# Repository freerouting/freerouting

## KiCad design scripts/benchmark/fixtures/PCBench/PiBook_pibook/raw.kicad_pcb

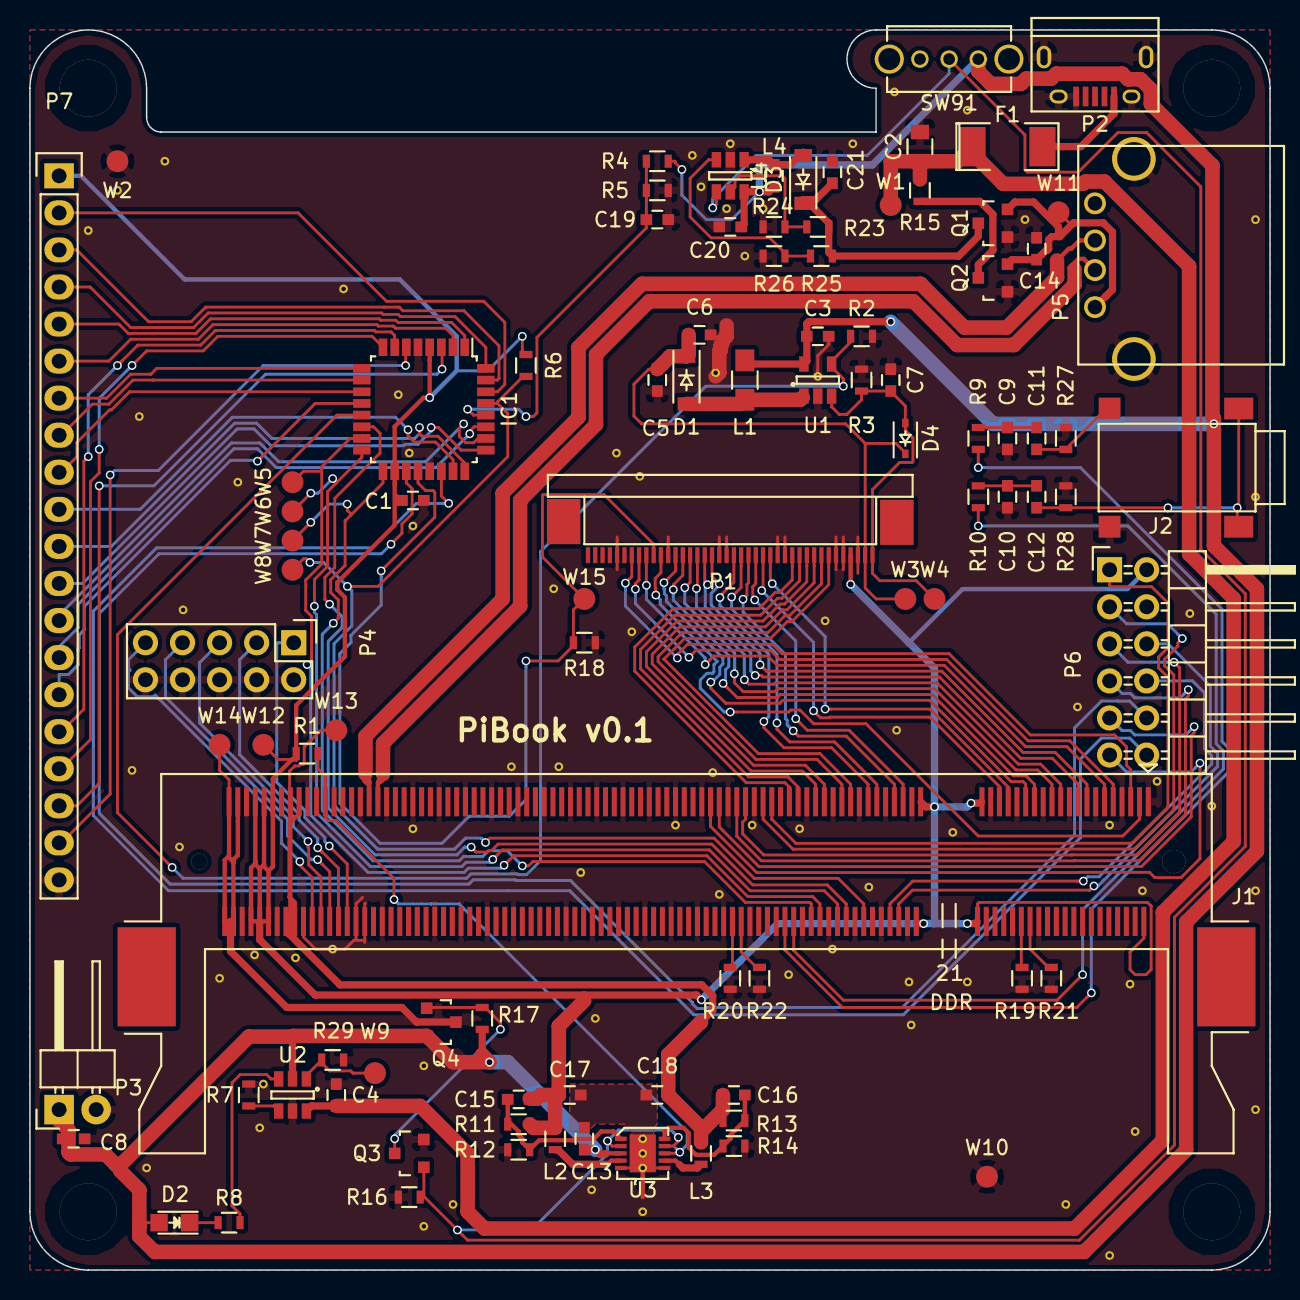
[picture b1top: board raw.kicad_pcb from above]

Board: 2 copper layers, 85.0 x 85.0 mm, 98 parts (0 on the bottom side), 103 nets.

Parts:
C1, C4, C5, C6, C7, C8, C11, C12, C20, C21: 1u; C_0603
C2: 22u; C_0805
C3: 4.7u; C_0603
C9, C10: 82n; C_0603
C13, C14, C17, C18: 10u; C_0603
C15, C16: 18p; C_0603
C19: 100n; C_0603
D1, D3: MBR0540T3G; SOD-123
D2: LED; LED_0805
D4: MM32Z24VT1G; SOD-323
F1: 2A; SMD-2010_Pol
IC1: ATTINY48-A; LQFP-32_7x7mm_Pitch0.8mm
J1: ComputeModule; Socket_SODIMM_DDR1-2_TE_1612618
J2: TRS_JACK_3PIN; TRS_3_SMD
L1: 6.8u; R_0805_HandSoldering
L2, L3: 2.2u; R_0603
L4: 10u; C_0603
MH1, MH2, MH3, MH4: Mounting_Hole; Mounting_hole_M3.5
P1: CONN_01X40; FPC40_BOTTOM
P2: USB_OTG; USB_Micro-B
P3: CONN_01X02; Pin_Header_Angled_1x02
P4: CONN_02X05; Pin_Header_Straight_2x05
P5: USB_A
P6: CONN_02X06; Pin_Header_Angled_2x06
P7: CONN_01X20; Pin_Header_Straight_1x20
Q1, Q2, Q4: Si2323DS; SOT-23
Q3: BSS138P; SOT-23
R1, R2, R4, R5, R6, R12, R14, R16, R17, R18, R19, R20, R21, R22, R27, R28: 100k; R_0603
R3: 12; R_0603
R7: 680; R_0603
R8: R; R_0603
R9, R10: 100; R_0603
R11: 450k; R_0603
R13: 200k; R_0603
R15: 0; R_0603
R23: 47k; R_0603
R24, R26, R29: 10k; R_0603
R25: 40k; R_0603
SW91: SPST; SPDT_SLIDE_SWITCH
TP1: Tie_point; tiepoint-0.3
U1: FAN5333; SOT-23-5
U2: BQ21040; SOT-23-6
U3: NCP1532; UDFN-10
U4: MIC2619YD6; SOT-23-6
W1: USB_VIN+; Measurement_Point_Round-SMD-Pad_Small
W2: USB_VIN-; Measurement_Point_Round-SMD-Pad_Small
W3: BACKL_A; Measurement_Point_Round-SMD-Pad_Small
W4: BACKL_K; Measurement_Point_Round-SMD-Pad_Small
W5, W6, W7, W8, W15: TEST_1P; Measurement_Point_Round-SMD-Pad_Small
W9: TS; Measurement_Point_Round-SMD-Pad_Small
W10: GND; Measurement_Point_Round-SMD-Pad_Small
W11: VUSB_OUT; Measurement_Point_Round-SMD-Pad_Small
W12: +3V3; Measurement_Point_Round-SMD-Pad_Small
W13: +1V8; Measurement_Point_Round-SMD-Pad_Small
W14: CM_VBAT; Measurement_Point_Round-SMD-Pad_Small

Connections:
+1V8: C16.1, C18.1, J1.183, J1.184, J1.185, J1.186, L3.2, R13.1, W13.1
+3V3: C1.1, C15.1, C17.1, IC1.4, IC1.18, J1.2, J1.39, J1.40, J1.41, J1.42, J1.189, J1.190, J1.191, J1.192, J1.193, J1.194, L2.2, P1.4, P6.2, P7.1, R1.1, R6.1, R11.1, W12.1
+5V: C21.1, D3.1, Q1.3, R23.1, R25.1
+BATT: C3.1, C8.1, C13.1, C20.1, D2.2, L1.1, L4.1, P3.1, Q4.2, R4.1, R17.1, SW91.1, U1.5, U2.2, U3.3, U4.6
+VUSB_IN: C2.1, C4.1, F1.1, R15.2, U2.6, W1.1
+VUSB_OUT: C14.1, P5.1, Q1.2, Q2.2, W11.1
/ANALOG0: IC1.19, P6.10
/ANALOG1: IC1.22, P6.12
/AUDIO_L_PWM: J1.70, R10.2
/AUDIO_R_PWM: J1.72, R9.2
/AVR_MISO: IC1.16, J1.60, W6.1
/AVR_MOSI: IC1.15, J1.64, W5.1
/AVR_SCK: IC1.17, J1.66, W7.1
/AVR_~CS: IC1.14, J1.58
/AVR_~RST: IC1.29, J1.54, R6.2, W8.1
/BACKL_A: C5.1, C6.1, D1.1, D4.1, P1.2, W3.1
/BACKL_K: C7.1, D4.2, P1.1, R3.1, U1.3, W4.1
/BACKL_PWM: IC1.13, R2.1, U1.4
/CM_RUN: J1.177, R1.2, U3.8
/CM_VBAT: J1.197, J1.198, J1.199, J1.200, Q4.3, W14.1
/KEY_C0: IC1.30, P7.2
/KEY_C1: IC1.31, P7.3
/KEY_C2: IC1.32, P7.4
/KEY_C3: IC1.1, P7.5
/KEY_C4: IC1.2, P7.6
/KEY_C5: IC1.9, P7.7
/KEY_C6: IC1.10, P7.8
/KEY_C7: IC1.11, P7.9
/KEY_C8: IC1.23, P7.10
/KEY_C9: IC1.24, P7.11
/KEY_C10: IC1.25, P7.12
/KEY_C11: IC1.26, P7.13
/KEY_R0: IC1.27, P7.14
/KEY_R1: IC1.12, P7.15
/KEY_R2: IC1.7, P7.16
/KEY_R3: IC1.8, P7.17
/KEY_R4: IC1.3, P7.18
/KEY_R5: IC1.6, P7.19
/LCD_B_2: J1.15, P1.23
/LCD_B_3: J1.17, P1.24
/LCD_B_4: J1.21, P1.25
/LCD_B_5: J1.23, P1.26
/LCD_B_6: J1.27, P1.27
/LCD_B_7: J1.29, P1.28
/LCD_CLK: J1.3, P1.30
/LCD_DEN: J1.5, P1.34
/LCD_DISP_ON: IC1.20, P1.31, R18.1, W15.1
/LCD_G_2: J1.33, P1.15
/LCD_G_3: J1.35, P1.16
/LCD_G_4: J1.45, P1.17
/LCD_G_5: J1.47, P1.18
/LCD_G_6: J1.51, P1.19
/LCD_G_7: J1.53, P1.20
/LCD_HSYNC: J1.11, P1.32
/LCD_R_2: J1.57, P1.7
/LCD_R_3: J1.59, P1.8
/LCD_R_4: J1.63, P1.9
/LCD_R_5: J1.65, P1.10
/LCD_R_6: J1.69, P1.11
/LCD_R_7: J1.71, P1.12
/LCD_VSYNC: J1.9, P1.33
/PWR_ENABLE: Q3.1, R16.1, SW91.2, U3.2, U3.9, U4.4
/UART_RX: J1.48, P6.8
/UART_TX: J1.46, P6.6
/USB_D+: J1.165, P5.2
/USB_D-: J1.167, P5.3
/USER_IO_0: J1.75, P6.1
/USER_IO_1: J1.77, P6.3
/USER_IO_2: J1.81, P6.5
/USER_IO_3: J1.83, P6.7
/USER_IO_4: J1.87, P6.9
/USER_IO_5: J1.89, P6.11
/VC_TCK: J1.180, P4.9
/VC_TDI: J1.174, P4.3
/VC_TDO: J1.178, P4.5
/VC_TMS: J1.176, P4.7
/VC_TRST_N: J1.172, P4.1
GND: C1.2, C2.2, C3.2, C4.2, C5.2, C6.2, C7.2, C8.2, C9.2, C10.2, C14.2, C19.2, C20.2, C21.2, IC1.5, IC1.21, J1.1, J1.7, J1.13, J1.19, J1.25, J1.26, J1.31, J1.32, J1.37, J1.38, J1.43, J1.44, J1.49, J1.50, J1.55, J1.56, J1.61, J1.62, J1.67, J1.68, J1.73, J1.74, J1.79, J1.80, J1.85, J1.86, J1.91, J1.92, J1.97, J1.98, J1.103, J1.104, J1.109, J1.110, J1.115, J1.116, J1.121, J1.122, J1.127, J1.133, J1.134, J1.139, J1.140, J1.145, J1.146, J1.151, J1.152, J1.157, J1.163, J1.164, J1.168, J1.169, J1.170, J1.181, J1.182, J1.187, J1.188, J1.195, J1.196, J2.2, P1.3, P1.5, P1.6, P1.13, P1.14, P1.21, P1.22, P1.29, P1.36, P2.5, P2.6, P3.2, P4.2, P4.4, P4.6, P4.8, P4.10, P5.4, P5.5, P6.4, P7.20, Q1.1, Q2.1, Q3.2, R2.2, R3.2, R5.2, R7.1, R12.2, R14.2, R16.2, R18.2, R19.2, R20.2, R21.2, R22.2, R24.2, R26.2, R27.2, R28.2, R29.1, TP1.2, U1.2, U2.5, U4.2, W2.1, W10.1
GNDPWR: C13.2, C17.2, C18.2, TP1.1, U3.5, U3.6
unnamed: C10.1, C12.1, R10.1
unnamed: C9.1, C11.1, R9.1
unnamed: C11.2, J2.3, R27.1
unnamed: C12.2, J2.1, R28.1
unnamed: C15.2, R11.2, R12.1, U3.1
unnamed: C16.2, R13.2, R14.1, U3.10
unnamed: C19.1, IC1.28, R4.2, R5.1
unnamed: D1.2, L1.2, U1.1
unnamed: D2.1, R8.1
unnamed: D3.2, L4.2, U4.1
unnamed: F1.2, P2.1
unnamed: J1.28, R21.1
unnamed: J1.30, R19.1
unnamed: J1.82, R22.1
unnamed: J1.84, R20.1
unnamed: L2.1, U3.4
unnamed: L3.1, U3.7
unnamed: Q2.3, R15.1
unnamed: Q3.3, Q4.1, R17.2
unnamed: R7.2, U2.4
unnamed: R8.2, U2.3
unnamed: R23.2, R24.1, U4.5
unnamed: R25.2, R26.1, U4.3
unnamed: R29.2, U2.1, W9.1

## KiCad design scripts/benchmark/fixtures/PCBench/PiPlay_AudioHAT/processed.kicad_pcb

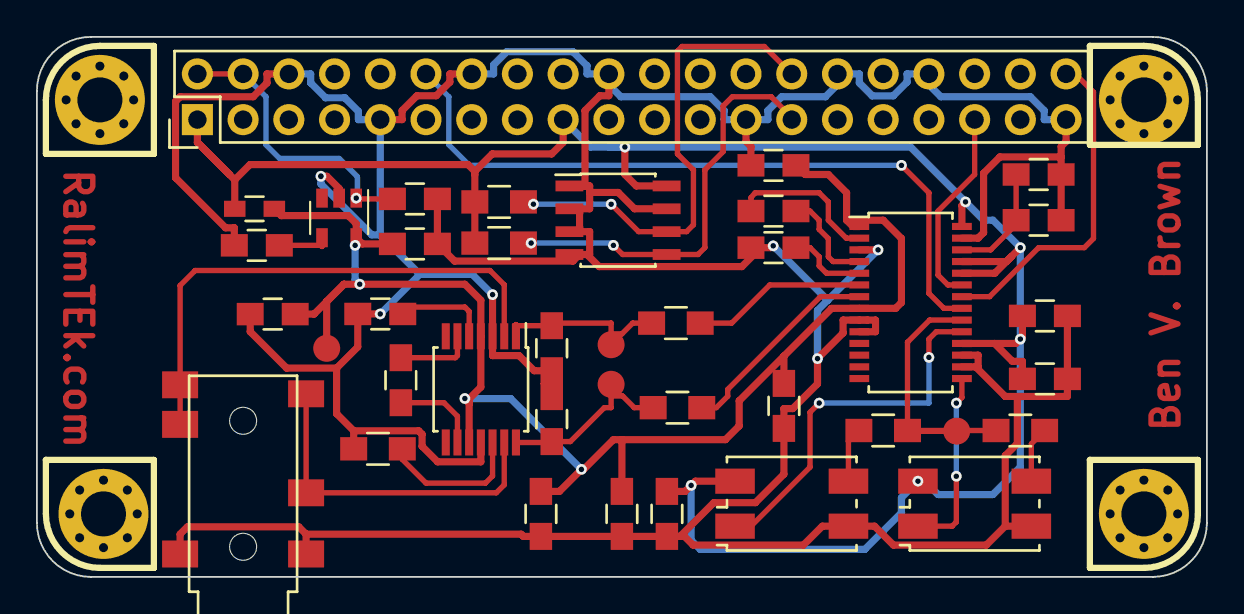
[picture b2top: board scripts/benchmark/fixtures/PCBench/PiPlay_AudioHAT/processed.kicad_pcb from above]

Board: 2 copper layers, 65.0 x 30.0 mm, 43 parts (0 on the bottom side), 29 nets.

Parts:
C101, C102, C106, C107, C110, C111, C112, C113, C114, C115, C116, C117, C118, C119: 0.1u; C_0805_HandSoldering
C103, C104, C105: 2.2uF; C_0805_HandSoldering
C108, C109: -; C_0805_HandSoldering
J101: RaspberryPi; Pin_Header_Straight_2x20
J102: JACK_TRS_6PINS; PJ311_6pin_3.5mm_SMD_Jack
JP101: Jumper_NO_Small; R_0603_HandSoldering
P101, P102, P103, P104: CONN_01X01; MountingHole_2.5mm_Pad_Via
R101, R102, R103, R104, R107: 470; R_0805_HandSoldering
R105, R106: 4k; R_0805_HandSoldering
U101: PCM5122; TSSOP-28_4.4x9.7mm_Pitch0.65mm
U102: 24C16; SOIC-8_3.9x4.9mm_Pitch1.27mm
U103: TPA6139A2; TSSOP-14_4.4x5mm_Pitch0.65mm
U104: LD3985G; SOT-23-5
W101: CLK; Measurement_Point_Round-SMD-Pad_Small
W102: 3.3V; Measurement_Point_Round-SMD-Pad_Small
W103: L; Measurement_Point_Round-SMD-Pad_Small
W104: R; Measurement_Point_Round-SMD-Pad_Small
X101: 24.576MHz; Crystal_SMD_7050_4Pads
X102: 22.5792MHz; Crystal_SMD_7050_4Pads

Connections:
/22MHZ_EN: U101.19, X102.1
/24MHZ_EN: U101.15, X101.1
/AVDD: C104.1, C111.1, C112.1, C113.1, C117.1, C119.1, JP101.2, U101.1, U101.8, U103.4, U103.10, U104.5, W102.1
/BCK: J101.12, U101.21
/DAC_L: C109.1, R101.2, U103.1, W103.1
/DAC_R: C108.2, R102.1, U103.14, W104.1
/DIN: J101.40, U101.22
/LRCLK: J101.35, U101.23
/OUT_L: J102.4, J102.5, U103.2
/OUT_R: J102.3, J102.6, U103.13
/SCK: R103.2, R104.2, U101.20, W101.1
GND: C101.2, C102.2, C104.2, C105.1, C106.2, C108.1, C109.2, C110.2, C111.2, C112.2, C113.2, C114.2, C115.2, C116.2, C117.2, C118.2, C119.2, J101.6, J101.9, J101.14, J101.20, J101.25, J101.30, J101.34, J101.39, J102.1, J102.2, R107.2, U101.3, U101.9, U101.10, U101.16, U101.17, U101.27, U102.1, U102.2, U102.3, U102.4, U102.7, U103.3, U103.11, U104.2, X101.2, X102.2
unnamed: C101.1, C102.1, U101.26
unnamed: C103.1, U101.2
unnamed: C103.2, U101.4
unnamed: C105.2, U101.5
unnamed: C106.1, U103.5
unnamed: C107.1, U103.9
unnamed: C107.2, U103.6
unnamed: C110.1, U104.4
unnamed: J101.27, R105.1, U102.5
unnamed: J101.28, R106.1, U102.6
unnamed: R101.1, U101.6
unnamed: R102.2, U101.7
unnamed: R103.1, X101.3
unnamed: R104.1, X102.3
unnamed: R107.1, U103.12
VCC: C118.1, J101.2, J101.4, U104.1
VDD: C114.1, C115.1, C116.1, J101.1, J101.17, JP101.1, R105.2, R106.2, U101.18, U101.24, U101.25, U101.28, U102.8, X101.4, X102.4

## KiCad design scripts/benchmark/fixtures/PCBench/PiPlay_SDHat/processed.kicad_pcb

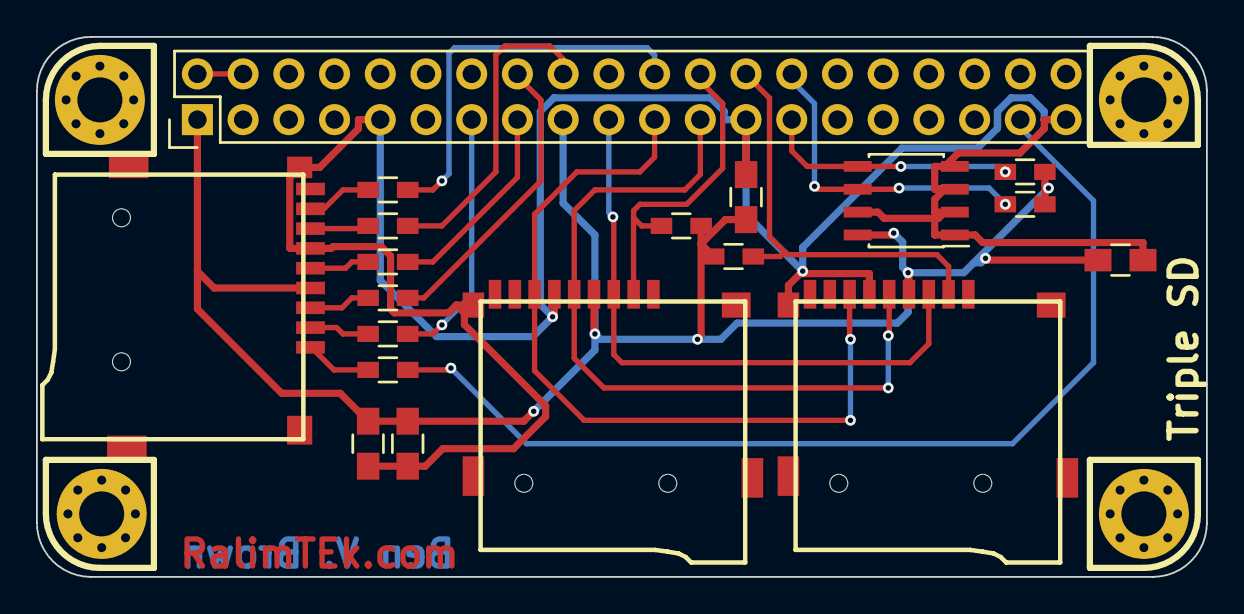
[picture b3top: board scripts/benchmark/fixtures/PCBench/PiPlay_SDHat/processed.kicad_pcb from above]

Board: 2 copper layers, 65.0 x 30.0 mm, 23 parts (0 on the bottom side), 22 nets.

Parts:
C101, C111, C112, C113: 0.1u; C_0805_HandSoldering
J101: RaspberryPi; Pin_Header_Straight_2x20
P101, P102, P103, P104: CONN_01X01; MountingHole_2.5mm_Pad_Via
R101, R102, R103, R104, R107, R108: 33; R_0603_HandSoldering
R105, R106, R109, R110: 4k; R_0603_HandSoldering
U101, U103: MicroSD_SPI_CD; GCT-MEM2055-00-190-01-A
U102: 24C16; SOIC-8_3.9x4.9mm_Pitch1.27mm
U104: Micro_SD_SDIO; GCT-MEM2055-00-190-01-A

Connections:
/CLK: J101.15, R102.1
/CMD: J101.16, R101.1
/CS0: J101.24, R109.2, U101.2
/CS1: J101.26, R110.2, U103.2
/DAT0: J101.18, R103.1
/DAT1: J101.22, R104.1
/DAT2: J101.37, R107.1
/DAT3: J101.13, R108.1
/ID_SCL: J101.28, R106.1, U102.6
/ID_SDA: J101.27, R105.1, U102.5
/MISO: J101.21, U101.7, U103.7
/MOSI: J101.19, U101.3, U103.3
/SCLK: J101.23, U101.5, U103.5
GND: C101.2, C111.2, C112.2, C113.2, J101.9, J101.25, J101.39, U101.6, U101.10, U102.1, U102.2, U102.3, U102.4, U102.7, U103.6, U103.10, U104.6, U104.10
unnamed: R101.2, U104.3
unnamed: R102.2, U104.5
unnamed: R103.2, U104.7
unnamed: R104.2, U104.8
unnamed: R107.2, U104.1
unnamed: R108.2, U104.2
VCC: J101.2, J101.4
VDD: C101.1, C111.1, C112.1, C113.1, J101.1, J101.17, R105.2, R106.2, R109.1, R110.1, U101.4, U102.8, U103.4, U104.4

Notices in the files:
scripts/benchmark/fixtures/PCBench/PiPlay_AudioHAT/processed.kicad_pcb:
License: CERN OHL V1.2
